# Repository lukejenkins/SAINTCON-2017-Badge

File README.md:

# SAINTCON-2017-Badge
Hardware files for the 2017 SAINTCON Badge.

This badge implemented the MiniBadge specification which is maintained [here](https://github.com/lukejenkins/minibadge).

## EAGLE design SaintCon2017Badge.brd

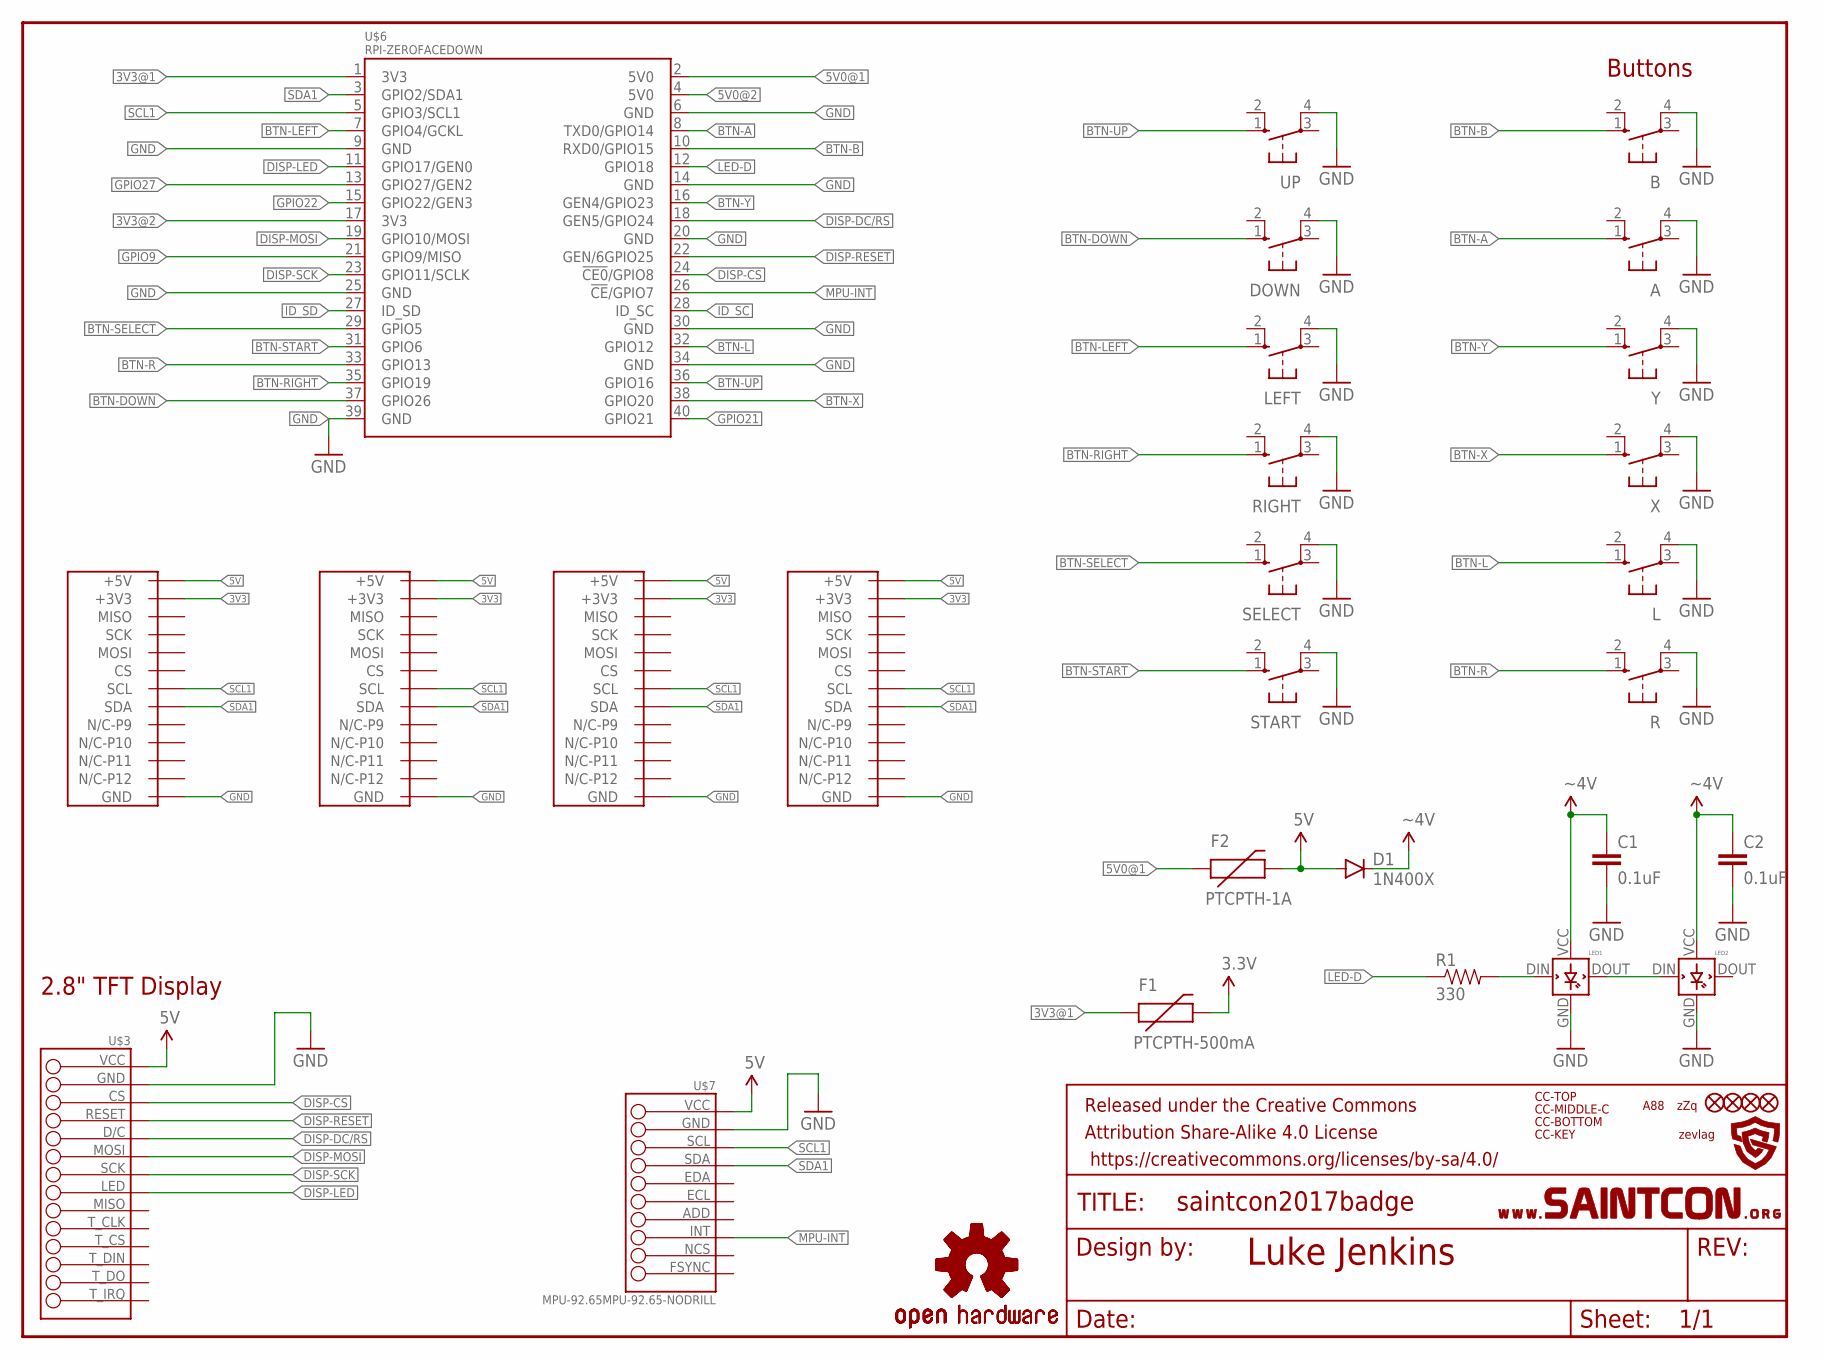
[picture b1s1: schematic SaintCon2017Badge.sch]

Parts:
A: 10-XX; B3F-10XX
B: 10-XX; B3F-10XX
C1, C2: 0.1uF; CAP-PTH-SMALL2
D1: 1N400X; DIODE-1N4001
DOWN: 10-XX; B3F-10XX
F1: PTCPTH-500mA; PTC
F2: PTCPTH-1A; PTC
FID1, FID2, FID3, FID4: FIDUCIAL1X2; FIDUCIAL-1X2
FRAME3: FRAME-LETTERNO_PACKAGE; DUMMY
L: 10-XX; B3F-10XX
LED1, LED2: WS2812WS2812-F8-FLIPPED-POWER; WS2812-F8-FLIPPED-POWER
LEFT: 10-XX; B3F-10XX
LOGO1: OSHW-LOGOS-COPPER; OSHW-LOGO-S_COPPER
LOGO2: OSHW-LOGOS; OSHW-LOGO-S
R: 10-XX; B3F-10XX
R1: 330; AXIAL-0.4
RIGHT: 10-XX; B3F-10XX
SELECT: 10-XX; B3F-10XX
START: 10-XX; B3F-10XX
U$1: AZZQ
U$2: A88
U$3: TFT28-14
U$4: SAINTCON-LOGO
U$5: SAINTCON-HEADERBLOCKLETTER; SAINTCON-HEADER-BLOCK-LETTER
U$6: RPI-ZEROFACEDOWN; RASP_PI_ZERO_BOARD_FULL
U$7: MPU-92.65MPU-92.65-NODRILL; MPU-92.65-NODRILL
U$8, U$9, U$10, U$11: BADGE64FOOTPRINT-SHINY; BADGE64-FOOTPRINT-SHINY
U$12: ZEVLAG2017SOLID-IS-BLACK; ZEVLAG2017-SOLID-IS-BLACK
U$13: CC-TOP; CURIOUSCODES-2017SAINTCON-TOP-LINE
U$14: CC-MIDDLE-C; CURIOUSCODES-2017SAINTCON-MIDDLE-C
U$15: CC-BOTTOM; CURIOUSCODES-2017SAINTCON-BOTTOM-LINE
U$16: CC-KEY; CUROIOUSCODES-KEY-HALF-INCH
UP: 10-XX; B3F-10XX
X: 10-XX; B3F-10XX
Y: 10-XX; B3F-10XX

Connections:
3V3: F1.P$2 (2), U$8.+3V3-P7 (+3V3), U$8.+3V3-P15 (+3V3), U$9.+3V3-P7 (+3V3), U$9.+3V3-P15 (+3V3), U$10.+3V3-P7 (+3V3), U$10.+3V3-P15 (+3V3), U$11.+3V3-P7 (+3V3), U$11.+3V3-P15 (+3V3)
3V3@1: F1.P$1 (1), U$6.1 (3V3)
3V3@2: U$6.17 (3V3)
5V: D1.A, F2.P$2 (2), U$3.VCC, U$7.VCC, U$8.+5V, U$9.+5V, U$10.+5V, U$11.+5V
5V0@1: F2.P$1 (1), U$6.2 (5V0)
5V0@2: U$6.4 (5V0)
BTN-A: A.1 (S), U$6.8 (TXD0/GPIO14)
BTN-B: B.1 (S), U$6.10 (RXD0/GPIO15)
BTN-DOWN: DOWN.1 (S), U$6.37 (GPIO26)
BTN-L: L.1 (S), U$6.32 (GPIO12)
BTN-LEFT: LEFT.1 (S), U$6.7 (GPIO4/GCKL)
BTN-R: R.1 (S), U$6.33 (GPIO13)
BTN-RIGHT: RIGHT.1 (S), U$6.35 (GPIO19)
BTN-SELECT: SELECT.1 (S), U$6.29 (GPIO5)
BTN-START: START.1 (S), U$6.31 (GPIO6)
BTN-UP: U$6.36 (GPIO16), UP.1 (S)
BTN-X: U$6.38 (GPIO20), X.1 (S)
BTN-Y: U$6.16 (GEN4/GPIO23), Y.1 (S)
DISP-CS: U$3.CS, U$6.24 (!CE0!/GPIO8)
DISP-DC/RS: U$3.D/C, U$6.18 (GEN5/GPIO24)
DISP-LED: U$3.LED, U$6.11 (GPIO17/GEN0)
DISP-MOSI: U$3.MOSI, U$6.19 (GPIO10/MOSI)
DISP-RESET: U$3.RESET, U$6.22 (GEN/6GPIO25)
DISP-SCK: U$3.SCK, U$6.23 (GPIO11/SCLK)
GND: A.4 (P1), B.4 (P1), C1.2, C2.2, DOWN.4 (P1), L.4 (P1), LED1.GND, LED2.GND, LEFT.4 (P1), R.4 (P1), RIGHT.4 (P1), SELECT.4 (P1), START.4 (P1), U$3.GND, U$6.6 (GND), U$6.9 (GND), U$6.14 (GND), U$6.20 (GND), U$6.25 (GND), U$6.30 (GND), U$6.34 (GND), U$6.39 (GND), U$7.GND, U$8.GND-P2 (GND), U$8.GND-P8 (GND), U$8.GND-P16 (GND), U$9.GND-P2 (GND), U$9.GND-P8 (GND), U$9.GND-P16 (GND), U$10.GND-P2 (GND), U$10.GND-P8 (GND), U$10.GND-P16 (GND), U$11.GND-P2 (GND), U$11.GND-P8 (GND), U$11.GND-P16 (GND), UP.4 (P1), X.4 (P1), Y.4 (P1)
GPIO9: U$6.21 (GPIO9/MISO)
GPIO21: U$6.40 (GPIO21)
GPIO22: U$6.15 (GPIO22/GEN3)
GPIO27: U$6.13 (GPIO27/GEN2)
ID_SC: U$6.28 (ID_SC)
ID_SD: U$6.27 (ID_SD)
LED1-LED2: LED1.DOUT, LED2.DIN
LED-D: R1.P$1 (1), U$6.12 (GPIO18)
MPU-INT: U$6.26 (!CE!/GPIO7), U$7.INT
R1-LED1: LED1.DIN, R1.P$2 (2)
SCL1: U$6.5 (GPIO3/SCL1), U$7.SCL, U$8.SCL, U$9.SCL, U$10.SCL, U$11.SCL
SDA1: U$6.3 (GPIO2/SDA1), U$7.SDA, U$8.SDA, U$9.SDA, U$10.SDA, U$11.SDA
VDD: C1.1, C2.1, D1.C, LED1.VCC (VDD), LED2.VCC (VDD)

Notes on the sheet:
Luke Jenkins
Buttons
2.8" TFT Display

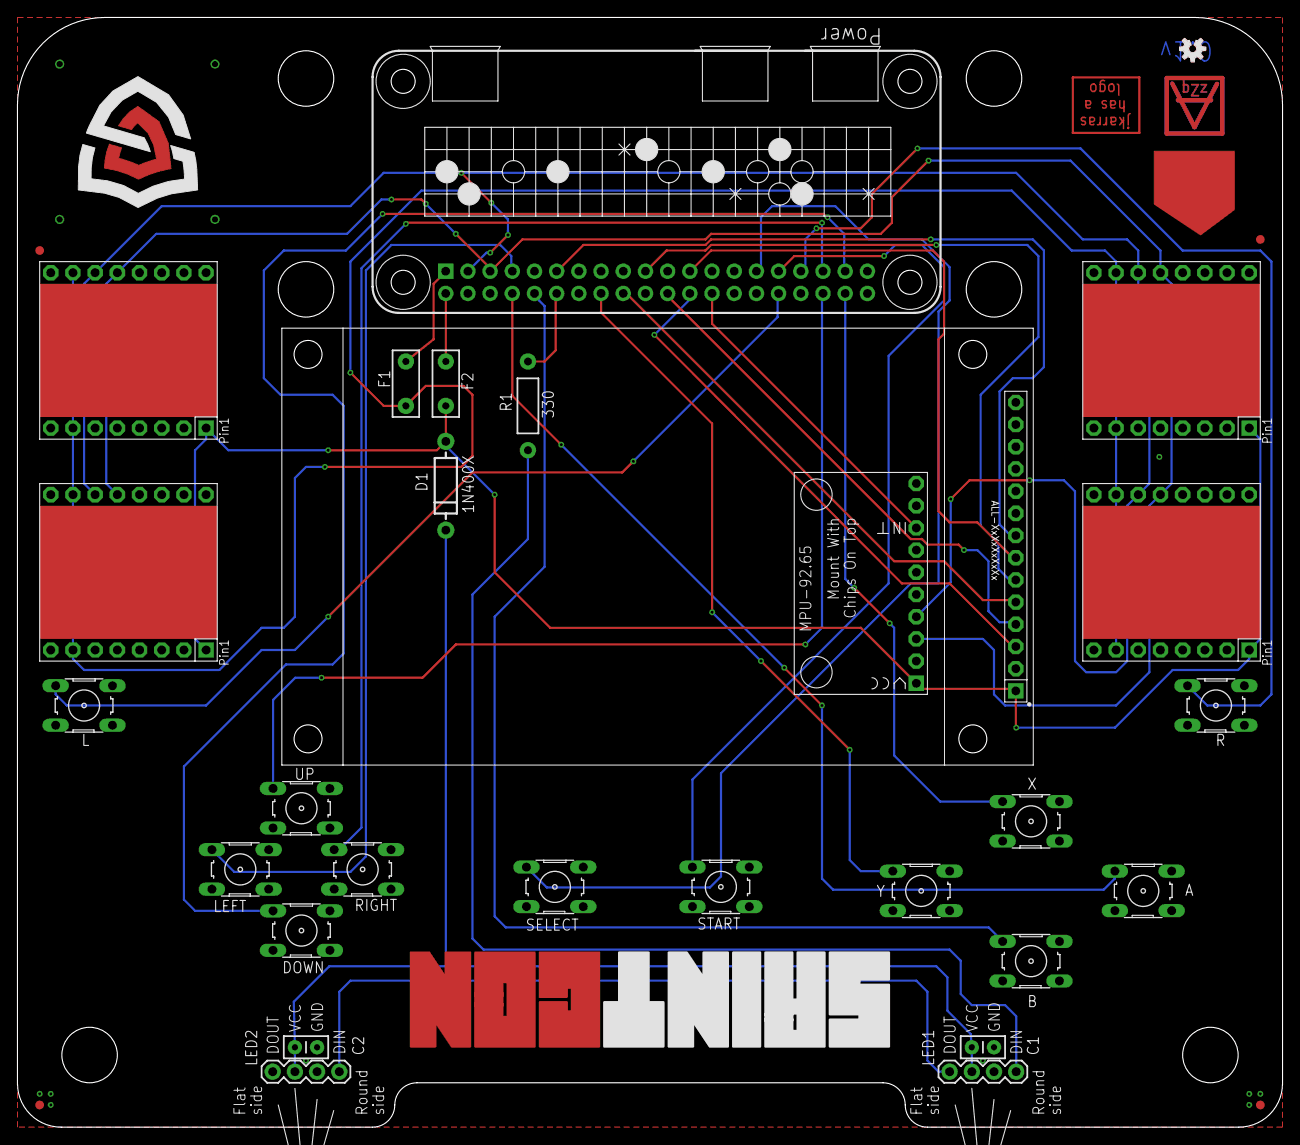
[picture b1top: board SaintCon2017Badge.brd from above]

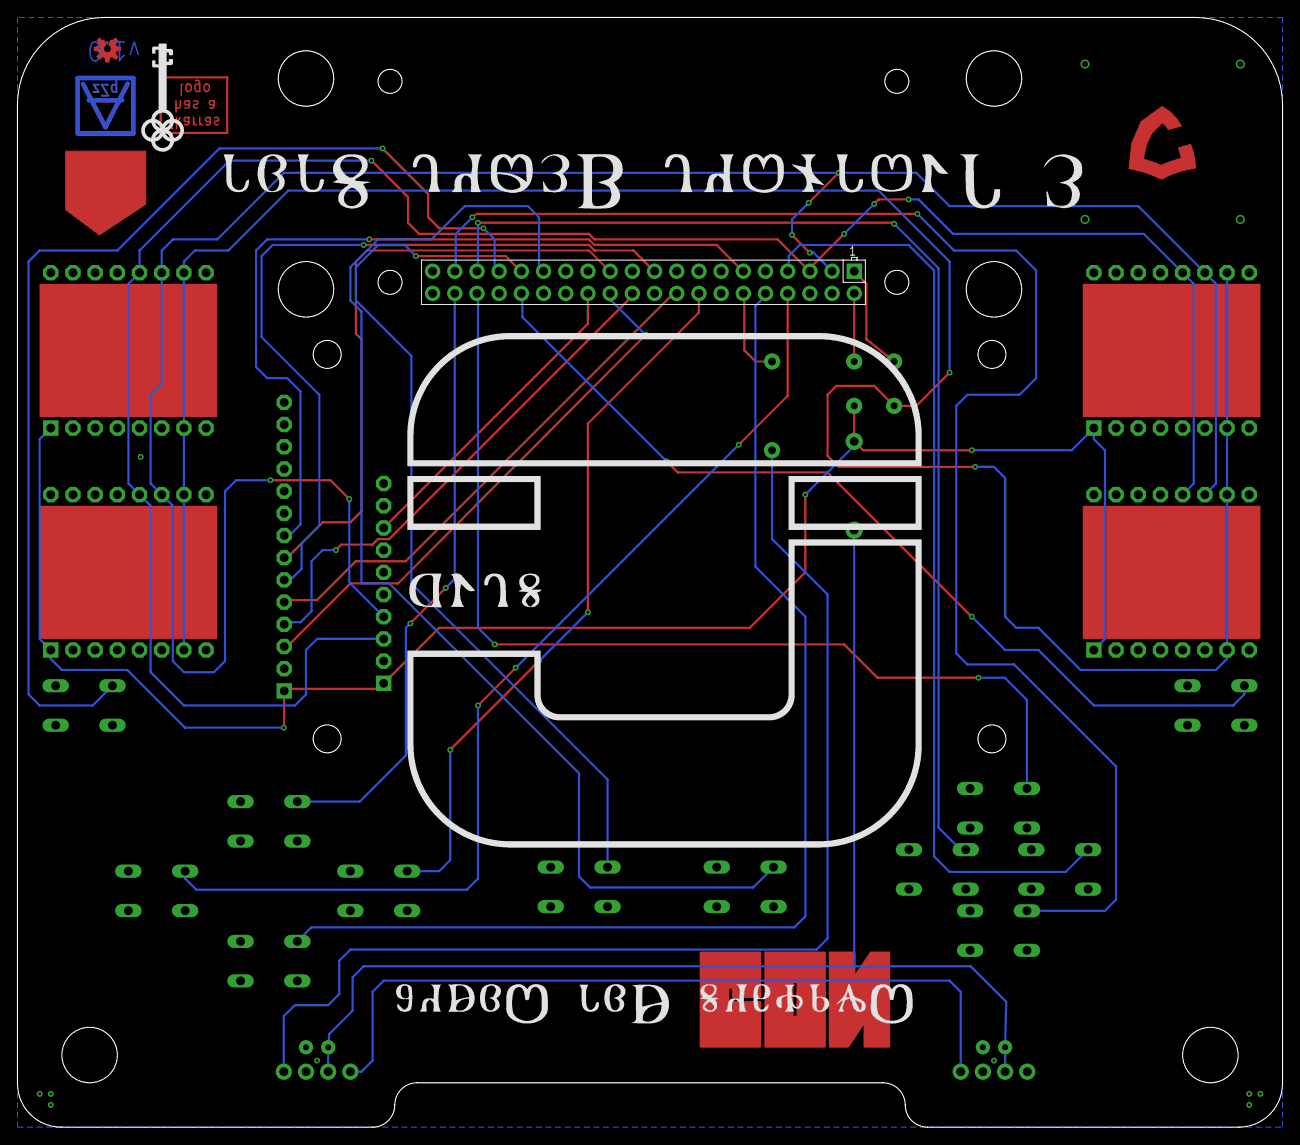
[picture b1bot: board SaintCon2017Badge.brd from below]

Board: 2 copper layers, 144.8 x 127.0 mm, 43 parts (4 on the bottom side), 30 nets.

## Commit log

2017-10-18 Upload eaglecad .brd and .sch files
2017-10-18 PDF Version of the Schematic
2017-10-18 link to the MiniBadge repo

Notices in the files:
parts and their libraries:
SparkFun-Aesthetics: Licensing: Creative Commons ShareAlike 4.0 International - https://creativecommons.org/licenses/by-sa/4.0
SparkFun-Aesthetics: Released under the Creative Commons Attribution Share-Alike 4.0 License
SparkFun-Aesthetics: https://creativecommons.org/licenses/by-sa/4.0
